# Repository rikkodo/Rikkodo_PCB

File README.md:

# Rikkodo_PCB

PCB関係

## 謝辞

作成には以下の方々のシンボルやフットプリント、知見を利用させていただいています。

Salicylic-acid3 氏のライブラリ[KiCAD_FootPrint](https://github.com/Salicylic-acid3/KiCAD_FootPrint)

koktoh氏のライブラリ [BrownSugar_KBD_KiCad_Library](https://github.com/koktoh/BrownSugar_KBD_KiCad_Library/tree/master)

palette-system氏のライブラリ [az1uball](https://github.com/palette-system/az1uball/tree/main/kicad)

Seeed-Studioのライブラリ [OPL_Kicad_Library](https://github.com/Seeed-Studio/OPL_Kicad_Library?tab=readme-ov-file#jump2)

SparkFunのライブラリ [SparkFun-KiCad-Libraries](https://github.com/sparkfun/SparkFun-KiCad-Libraries.git)

DreaM117er氏のライブラリ [DreaM117er KiCAD Library](https://github.com/DreaM117er/DreaM117er-keebLibrary.git)

Tomotsugu Kaneko氏のライブラリ [BOB-PMW3360-SUMI](https://github.com/snize/BOB-PMW3360-SUMI)

Tomotsugu Kaneko氏のライブラリ [BOB-PMW3360-SEIBOKU](https://github.com/snize/BOB-PMW3610-SEIBOKU)

## ライセンス

### BOB-PMW3360-SUMI、BOB-PMW3360-SEIBOKU

This project is licensed under the CERN OHL-P v2. You may use, distribute, and modify this design under the terms of the CERN OHL-P v2. Original design by snize.

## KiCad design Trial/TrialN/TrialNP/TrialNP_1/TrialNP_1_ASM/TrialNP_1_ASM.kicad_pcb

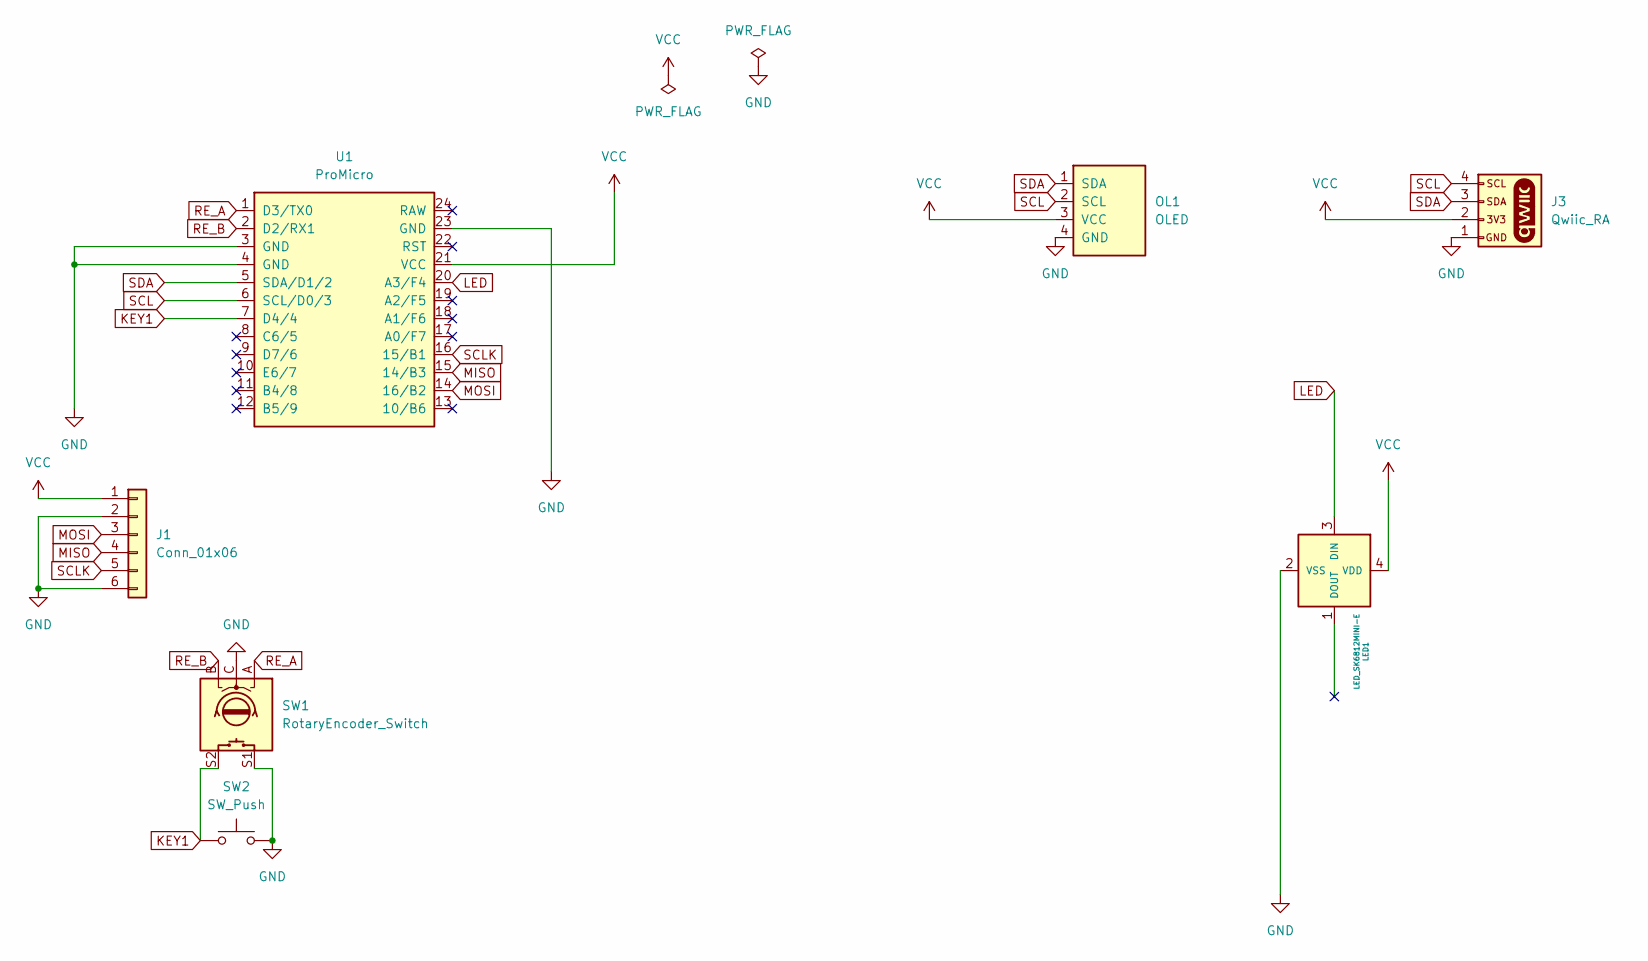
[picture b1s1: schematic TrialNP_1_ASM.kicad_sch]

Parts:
J1: Conn_01x06; PinHeader_1x06_P2.54mm_Vertical
J3: Qwiic_RA; JST_SMD_1.0mm-4_Black
LED1: LED_SK6812MINI-E; LED_SK6812MINI-E_UG
OL1: OLED; OLED_center_display
SW1: RotaryEncoder_Switch; RotaryEncoder_EC11-Switch
SW2: SW_Push; CherryMX_Solder_1u
U1: ProMicro; ProMicro_r

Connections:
GND: J1.2, J1.6, J3.1, LED1.2 (VSS), OL1.4 (GND), SW1.C, SW1.S1, SW2.2, U1.3 (GND), U1.4 (GND), U1.23 (GND)
KEY1: SW1.S2, SW2.1, U1.7 (D4/4)
LED: LED1.3 (DIN), U1.20 (A3/F4)
MISO: J1.4, U1.15 (14/B3)
MOSI: J1.3, U1.14 (16/B2)
RE_A: SW1.A, U1.1 (D3/TX0)
RE_B: SW1.B, U1.2 (D2/RX1)
SCL: J3.4, OL1.2 (SCL), U1.6 (SCL/D0/3)
SCLK: J1.5, U1.16 (15/B1)
SDA: J3.3, OL1.1 (SDA), U1.5 (SDA/D1/2)
VCC: J1.1, J3.2, LED1.4 (VDD), OL1.3 (VCC), U1.21 (VCC)

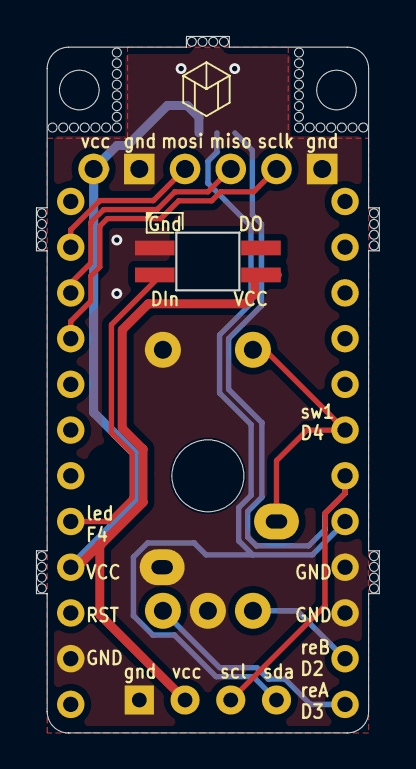
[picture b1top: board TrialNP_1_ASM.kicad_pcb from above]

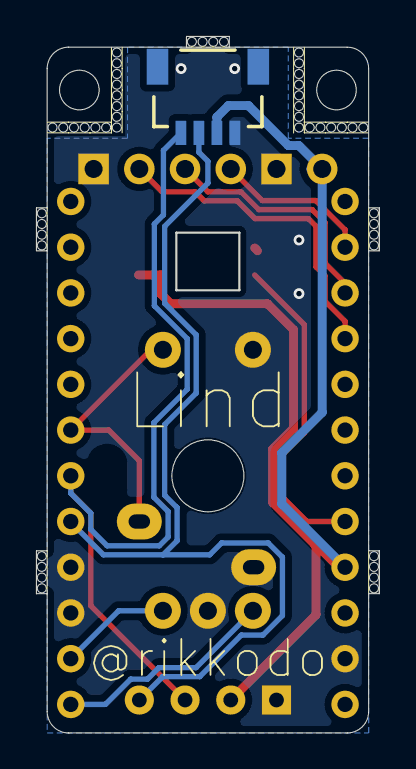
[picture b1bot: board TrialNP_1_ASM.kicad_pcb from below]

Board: 2 copper layers, 19.0 x 38.6 mm, 9 parts (3 on the bottom side), 11 nets.

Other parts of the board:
Ref**: Val**; m2_Screw_Hole
Ref**#2: Val**; m2_Screw_Hole

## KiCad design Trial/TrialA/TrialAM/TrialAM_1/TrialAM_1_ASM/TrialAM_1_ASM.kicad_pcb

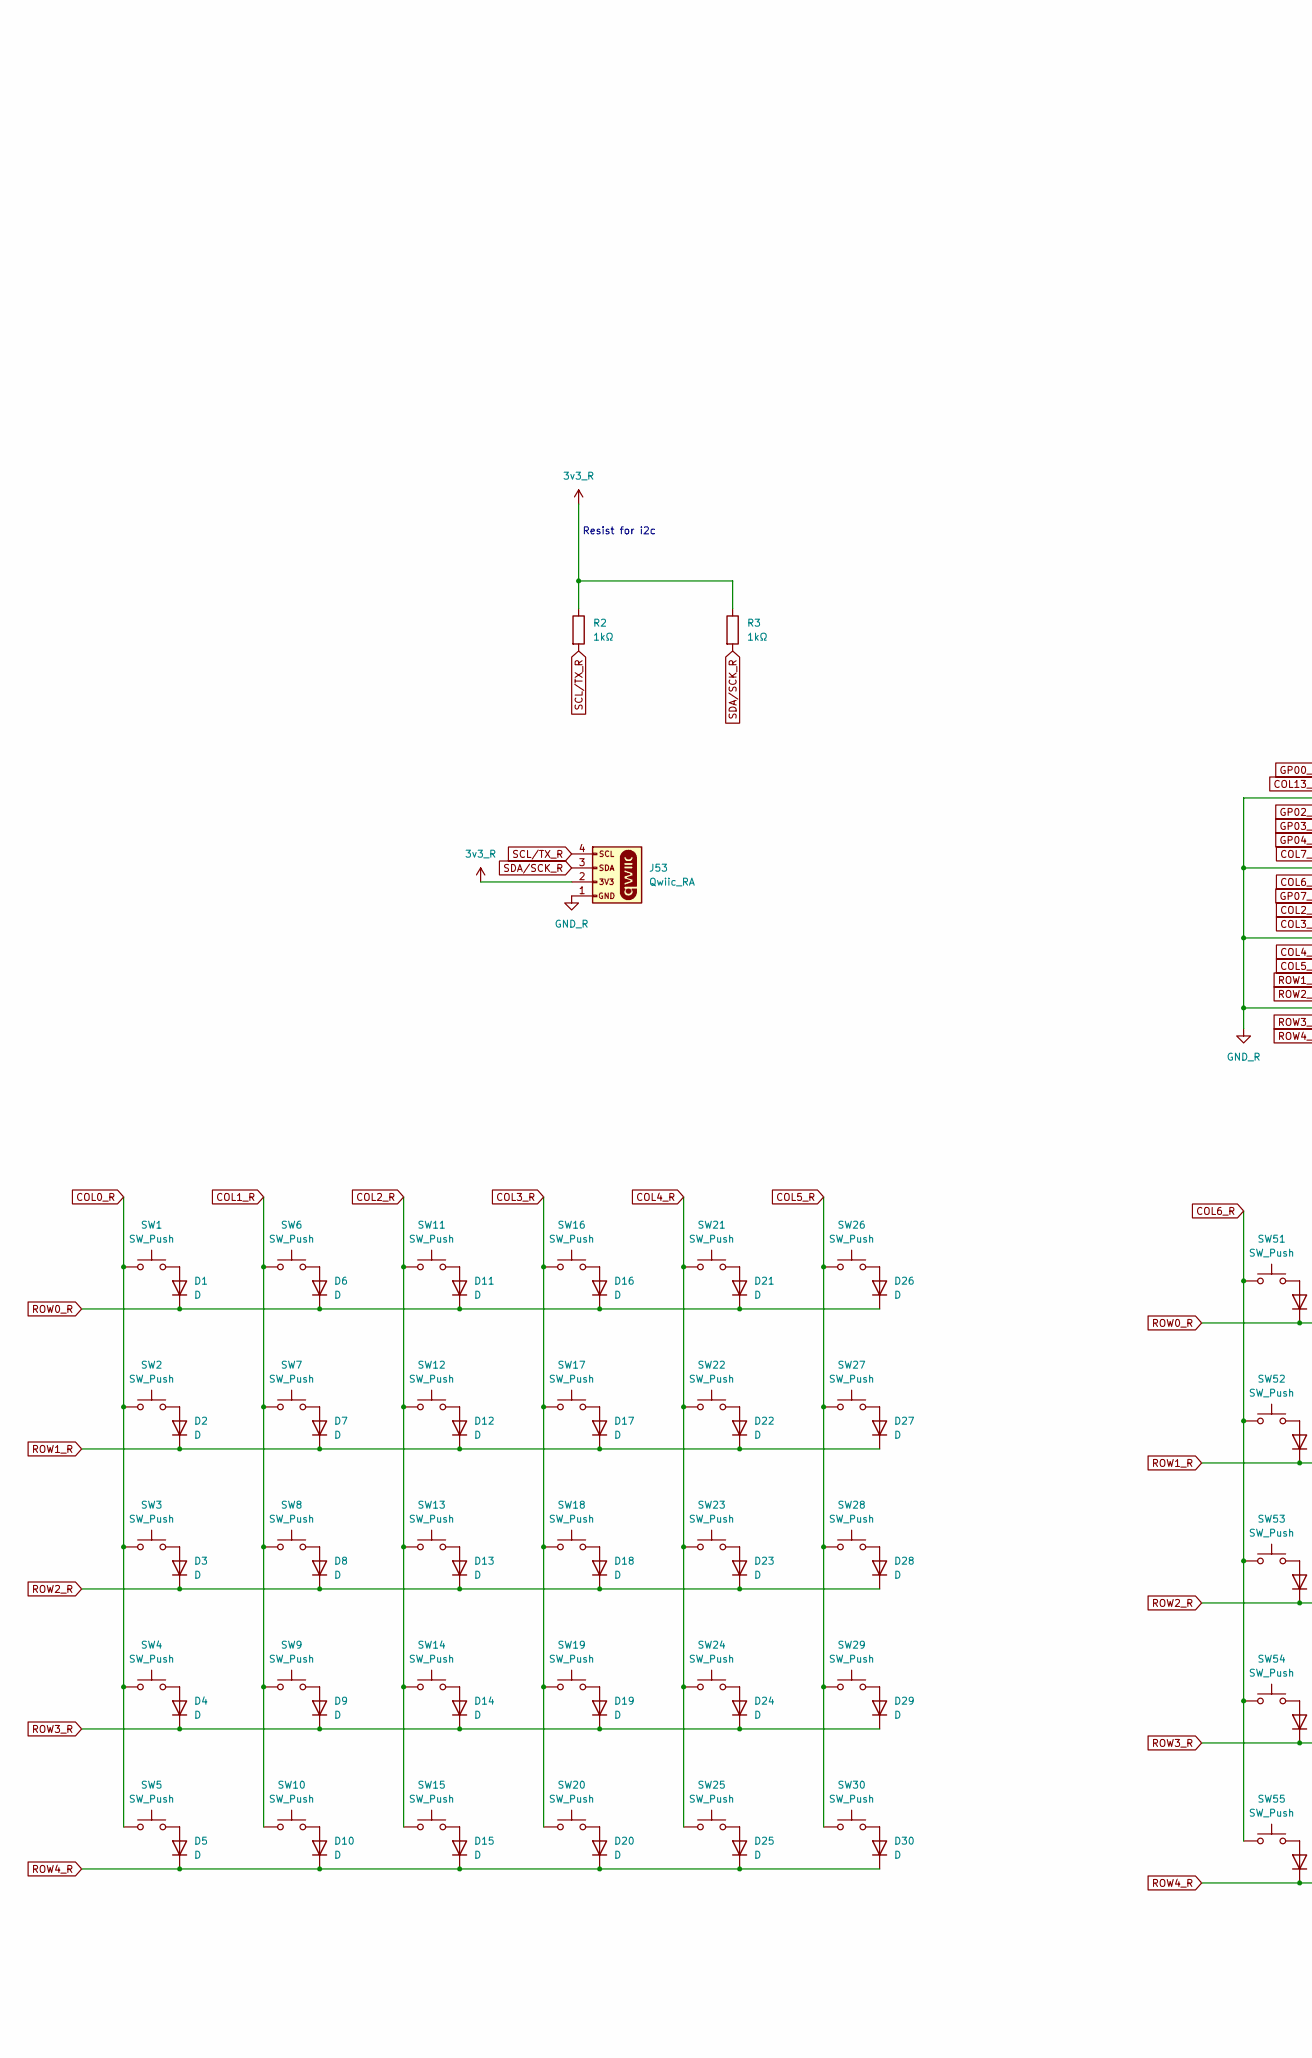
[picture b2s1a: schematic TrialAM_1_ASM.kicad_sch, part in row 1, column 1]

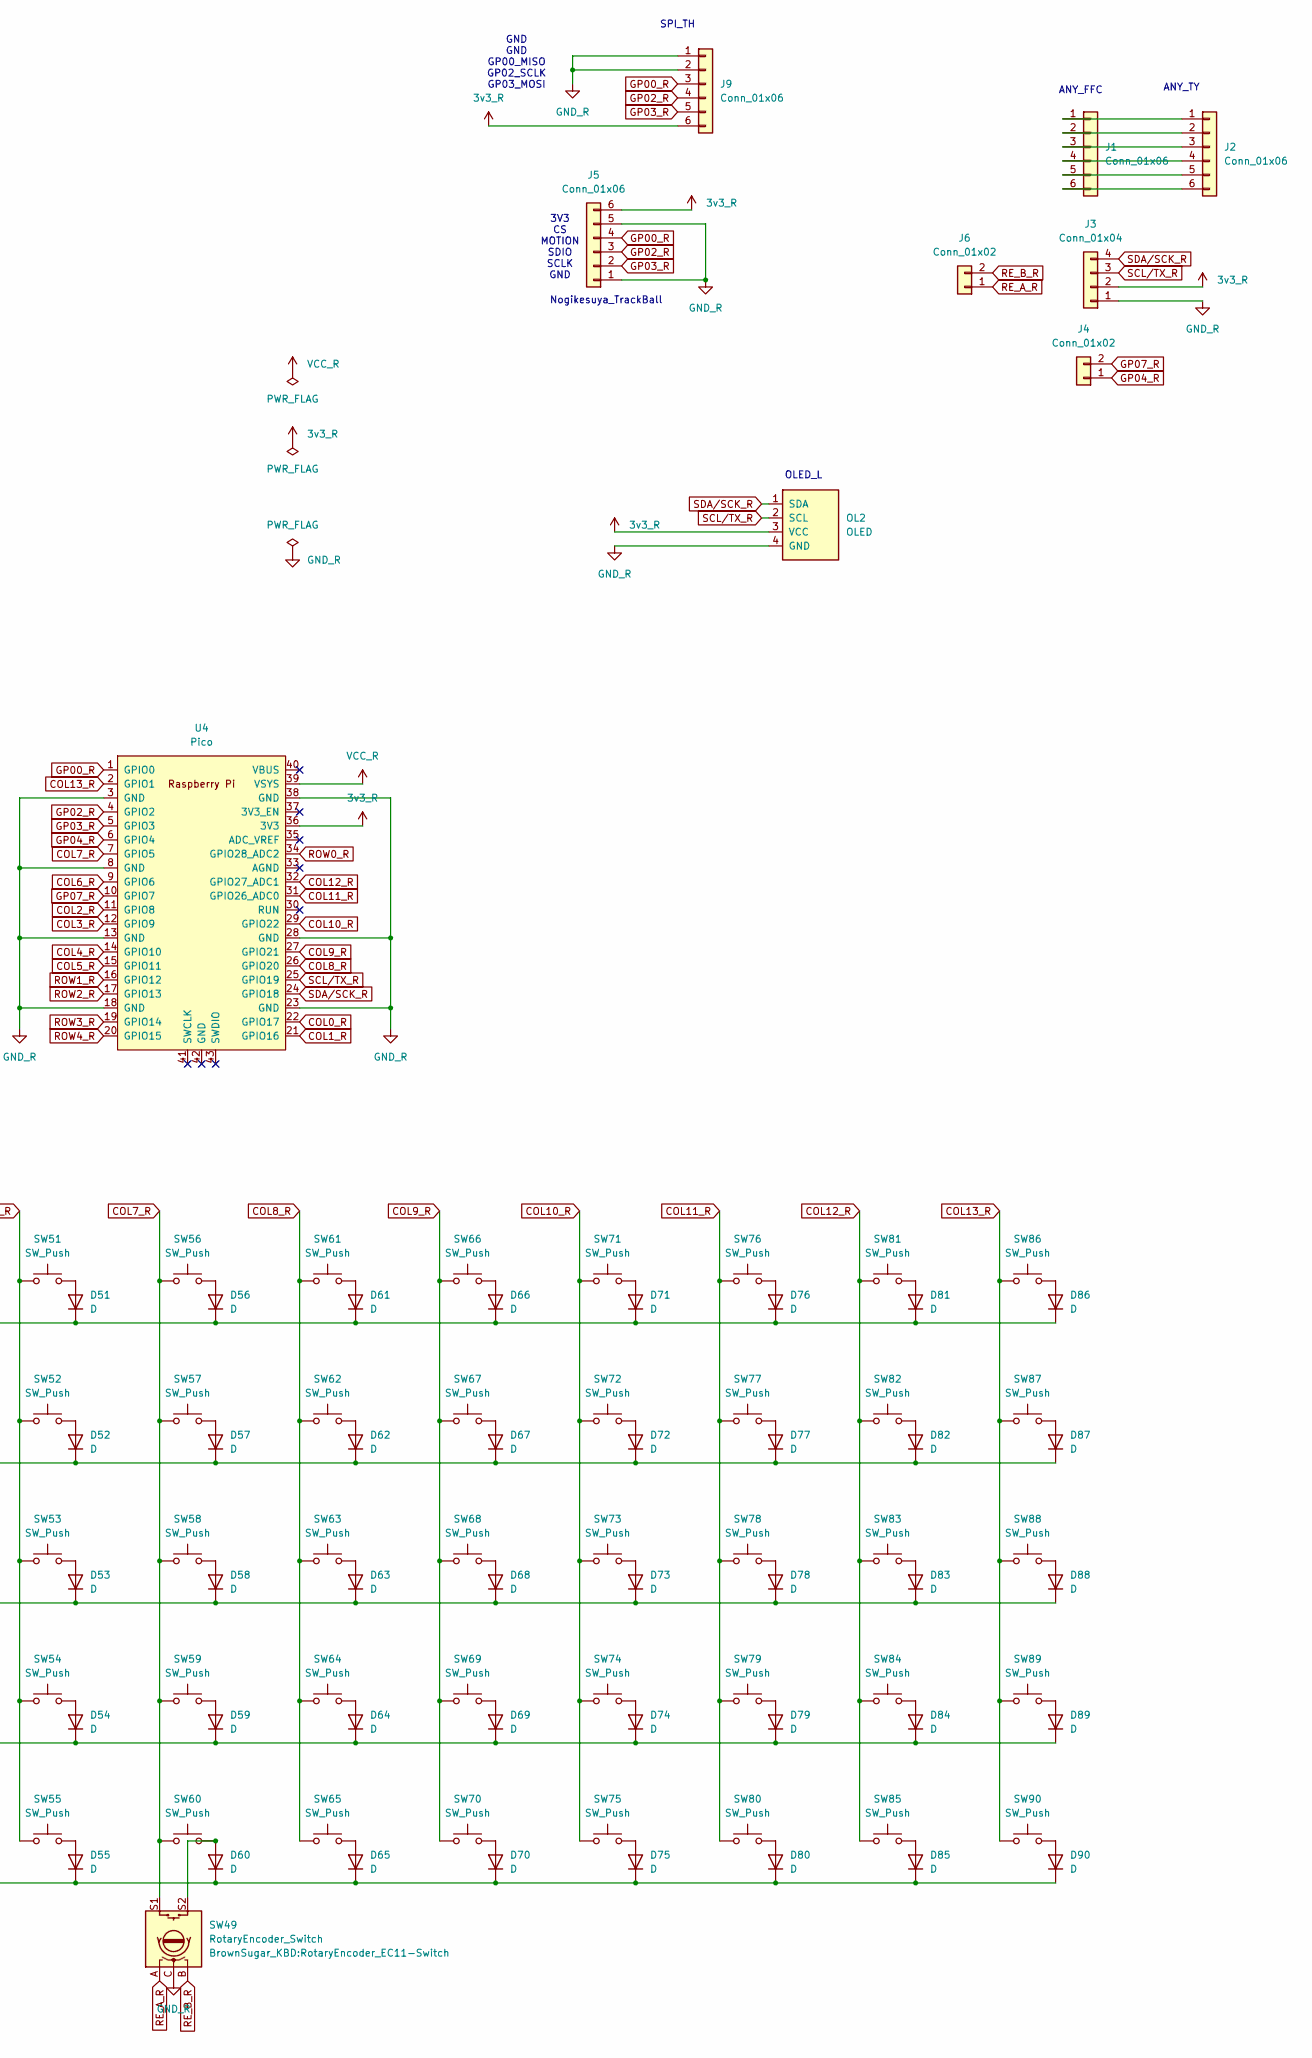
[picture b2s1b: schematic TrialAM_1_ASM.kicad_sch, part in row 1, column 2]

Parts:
D1, D2, D3, D4, D5, D6, D7, D8, D9, D10, D11, D12, D13, D14, D15, D16, D17, D18, D19, D20, D21, D22, D23, D24, D25, D26, D27, D28, D29, D30, D51, D52, D53, D54, D55, D56, D57, D58, D59, D60, D61, D62, D63, D64, D65, D66, D67, D68, D69, D70, D71, D72, D73, D74, D75, D76, D77, D78, D79, D80, D81, D82, D83, D84, D85, D86, D87, D88, D89, D90: D; Diode_SMD
J1, J5: Conn_01x06; Hirose_FH12-6S-0.5SH_1x06-1MP_P0.50mm_Horizontal
J2, J9: Conn_01x06; PinHeader_1x06_P2.54mm_Vertical
J3: Conn_01x04; PinHeader_1x04_P2.54mm_Vertical
J4, J6: Conn_01x02; PinHeader_1x02_P2.54mm_Vertical
J53: Qwiic_RA; JST_SMD_1.0mm-4_Black
OL2: OLED; OLED_center_display
R2, R3: 1kΩ; R_0603_1608Metric
SW1, SW2, SW3, SW4, SW5, SW6, SW7, SW8, SW9, SW10, SW11, SW12, SW13, SW14, SW15, SW16, SW17, SW18, SW19, SW20, SW21, SW22, SW23, SW24, SW26, SW27, SW28, SW29, SW51, SW52, SW54, SW56, SW57, SW58, SW59, SW61, SW62, SW63, SW64, SW65, SW66, SW67, SW68, SW69, SW70, SW71, SW72, SW73, SW74, SW75, SW76, SW77, SW78, SW79, SW80, SW81, SW82, SW83, SW84, SW85, SW86, SW87, SW89, SW90: SW_Push; rkd_pushsw_2_1u
SW25, SW60, SW88: SW_Push; rkd_pushsw_2_2u
SW30, SW53, SW55: SW_Push; rkd_pushsw_2_1.25u
SW49: RotaryEncoder_Switch; RotaryEncoder_EC11-Switch
U4: Pico; rkd_RPi_Pico_TH_NODBG

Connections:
3v3_R: J3.2, J5.6, J9.6, J53.2, OL2.3 (VCC), R2.1, R3.1, U4.36 (3V3)
COL0_R: SW1.2, SW2.2, SW3.2, SW4.2, SW5.2, U4.22 (GPIO17)
COL1_R: SW6.2, SW7.2, SW8.2, SW9.2, SW10.2, U4.21 (GPIO16)
COL2_R: SW11.2, SW12.2, SW13.2, SW14.2, SW15.2, U4.11 (GPIO8)
COL3_R: SW16.2, SW17.2, SW18.2, SW19.2, SW20.2, U4.12 (GPIO9)
COL4_R: SW21.2, SW22.2, SW23.2, SW24.2, SW25.2, U4.14 (GPIO10)
COL5_R: SW26.2, SW27.2, SW28.2, SW29.2, SW30.2, U4.15 (GPIO11)
COL6_R: SW51.2, SW52.2, SW53.2, SW54.2, SW55.2, U4.9 (GPIO6)
COL7_R: SW49.S1, SW56.2, SW57.2, SW58.2, SW59.2, SW60.2, U4.7 (GPIO5)
COL8_R: SW61.2, SW62.2, SW63.2, SW64.2, SW65.2, U4.26 (GPIO20)
COL9_R: SW66.2, SW67.2, SW68.2, SW69.2, SW70.2, U4.27 (GPIO21)
COL10_R: SW71.2, SW72.2, SW73.2, SW74.2, SW75.2, U4.29 (GPIO22)
COL11_R: SW76.2, SW77.2, SW78.2, SW79.2, SW80.2, U4.31 (GPIO26_ADC0)
COL12_R: SW81.2, SW82.2, SW83.2, SW84.2, SW85.2, U4.32 (GPIO27_ADC1)
COL13_R: SW86.2, SW87.2, SW88.2, SW89.2, SW90.2, U4.2 (GPIO1)
GND_R: J3.1, J5.1, J5.5, J9.1, J9.2, J53.1, OL2.4 (GND), SW49.C, U4.3 (GND), U4.8 (GND), U4.13 (GND), U4.18 (GND), U4.23 (GND), U4.28 (GND), U4.38 (GND)
GP00_R: J5.4, J9.3, U4.1 (GPIO0)
GP02_R: J5.3, J9.4, U4.4 (GPIO2)
GP03_R: J5.2, J9.5, U4.5 (GPIO3)
GP04_R: J4.1, U4.6 (GPIO4)
GP07_R: J4.2, U4.10 (GPIO7)
unnamed: D1.2 (A), SW1.1
unnamed: D2.2 (A), SW2.1
unnamed: D3.2 (A), SW3.1
unnamed: D4.2 (A), SW4.1
unnamed: D5.2 (A), SW5.1
unnamed: D6.2 (A), SW6.1
unnamed: D7.2 (A), SW7.1
unnamed: D8.2 (A), SW8.1
unnamed: D9.2 (A), SW9.1
unnamed: D10.2 (A), SW10.1
unnamed: D11.2 (A), SW11.1
unnamed: D12.2 (A), SW12.1
unnamed: D13.2 (A), SW13.1
unnamed: D14.2 (A), SW14.1
unnamed: D15.2 (A), SW15.1
unnamed: D16.2 (A), SW16.1
unnamed: D17.2 (A), SW17.1
unnamed: D18.2 (A), SW18.1
unnamed: D19.2 (A), SW19.1
unnamed: D20.2 (A), SW20.1
unnamed: D21.2 (A), SW21.1
unnamed: D22.2 (A), SW22.1
unnamed: D23.2 (A), SW23.1
unnamed: D24.2 (A), SW24.1
unnamed: D25.2 (A), SW25.1
unnamed: D26.2 (A), SW26.1
unnamed: D27.2 (A), SW27.1
unnamed: D28.2 (A), SW28.1
unnamed: D29.2 (A), SW29.1
unnamed: D30.2 (A), SW30.1
unnamed: D51.2 (A), SW51.1
unnamed: D52.2 (A), SW52.1
unnamed: D53.2 (A), SW53.1
unnamed: D54.2 (A), SW54.1
unnamed: D55.2 (A), SW55.1
unnamed: D56.2 (A), SW56.1
unnamed: D57.2 (A), SW57.1
unnamed: D58.2 (A), SW58.1
unnamed: D59.2 (A), SW59.1
unnamed: D60.2 (A), SW49.S2, SW60.1
unnamed: D61.2 (A), SW61.1
unnamed: D62.2 (A), SW62.1
unnamed: D63.2 (A), SW63.1
unnamed: D64.2 (A), SW64.1
unnamed: D65.2 (A), SW65.1
unnamed: D66.2 (A), SW66.1
unnamed: D67.2 (A), SW67.1
unnamed: D68.2 (A), SW68.1
unnamed: D69.2 (A), SW69.1
unnamed: D70.2 (A), SW70.1
unnamed: D71.2 (A), SW71.1
unnamed: D72.2 (A), SW72.1
unnamed: D73.2 (A), SW73.1
unnamed: D74.2 (A), SW74.1
unnamed: D75.2 (A), SW75.1
unnamed: D76.2 (A), SW76.1
unnamed: D77.2 (A), SW77.1
unnamed: D78.2 (A), SW78.1
unnamed: D79.2 (A), SW79.1
unnamed: D80.2 (A), SW80.1
unnamed: D81.2 (A), SW81.1
unnamed: D82.2 (A), SW82.1
unnamed: D83.2 (A), SW83.1
unnamed: D84.2 (A), SW84.1
unnamed: D85.2 (A), SW85.1
unnamed: D86.2 (A), SW86.1
unnamed: D87.2 (A), SW87.1
unnamed: D88.2 (A), SW88.1
unnamed: D89.2 (A), SW89.1
unnamed: D90.2 (A), SW90.1
unnamed: J1.1, J2.1
unnamed: J1.2, J2.2
unnamed: J1.3, J2.3
unnamed: J1.4, J2.4
unnamed: J1.5, J2.5
unnamed: J1.6, J2.6
RE_A_R: J6.1, SW49.A
RE_B_R: J6.2, SW49.B
ROW0_R: D1.1 (K), D6.1 (K), D11.1 (K), D16.1 (K), D21.1 (K), D26.1 (K), D51.1 (K), D56.1 (K), D61.1 (K), D66.1 (K), D71.1 (K), D76.1 (K), D81.1 (K), D86.1 (K), U4.34 (GPIO28_ADC2)
ROW1_R: D2.1 (K), D7.1 (K), D12.1 (K), D17.1 (K), D22.1 (K), D27.1 (K), D52.1 (K), D57.1 (K), D62.1 (K), D67.1 (K), D72.1 (K), D77.1 (K), D82.1 (K), D87.1 (K), U4.16 (GPIO12)
ROW2_R: D3.1 (K), D8.1 (K), D13.1 (K), D18.1 (K), D23.1 (K), D28.1 (K), D53.1 (K), D58.1 (K), D63.1 (K), D68.1 (K), D73.1 (K), D78.1 (K), D83.1 (K), D88.1 (K), U4.17 (GPIO13)
ROW3_R: D4.1 (K), D9.1 (K), D14.1 (K), D19.1 (K), D24.1 (K), D29.1 (K), D54.1 (K), D59.1 (K), D64.1 (K), D69.1 (K), D74.1 (K), D79.1 (K), D84.1 (K), D89.1 (K), U4.19 (GPIO14)
ROW4_R: D5.1 (K), D10.1 (K), D15.1 (K), D20.1 (K), D25.1 (K), D30.1 (K), D55.1 (K), D60.1 (K), D65.1 (K), D70.1 (K), D75.1 (K), D80.1 (K), D85.1 (K), D90.1 (K), U4.20 (GPIO15)
SCL/TX_R: J3.3, J53.4, OL2.2 (SCL), R2.2, U4.25 (GPIO19)
SDA/SCK_R: J3.4, J53.3, OL2.1 (SDA), R3.2, U4.24 (GPIO18)
VCC_R: U4.39 (VSYS)

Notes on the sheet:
GND GND GP00_MISO GP02_SCLK GP03_MOSI
Resist for i2c
ANY_TY
3V3 CS MOTION SDIO SCLK GND
ANY_FFC
Nogikesuya_TrackBall
SPI_TH
OLED_L

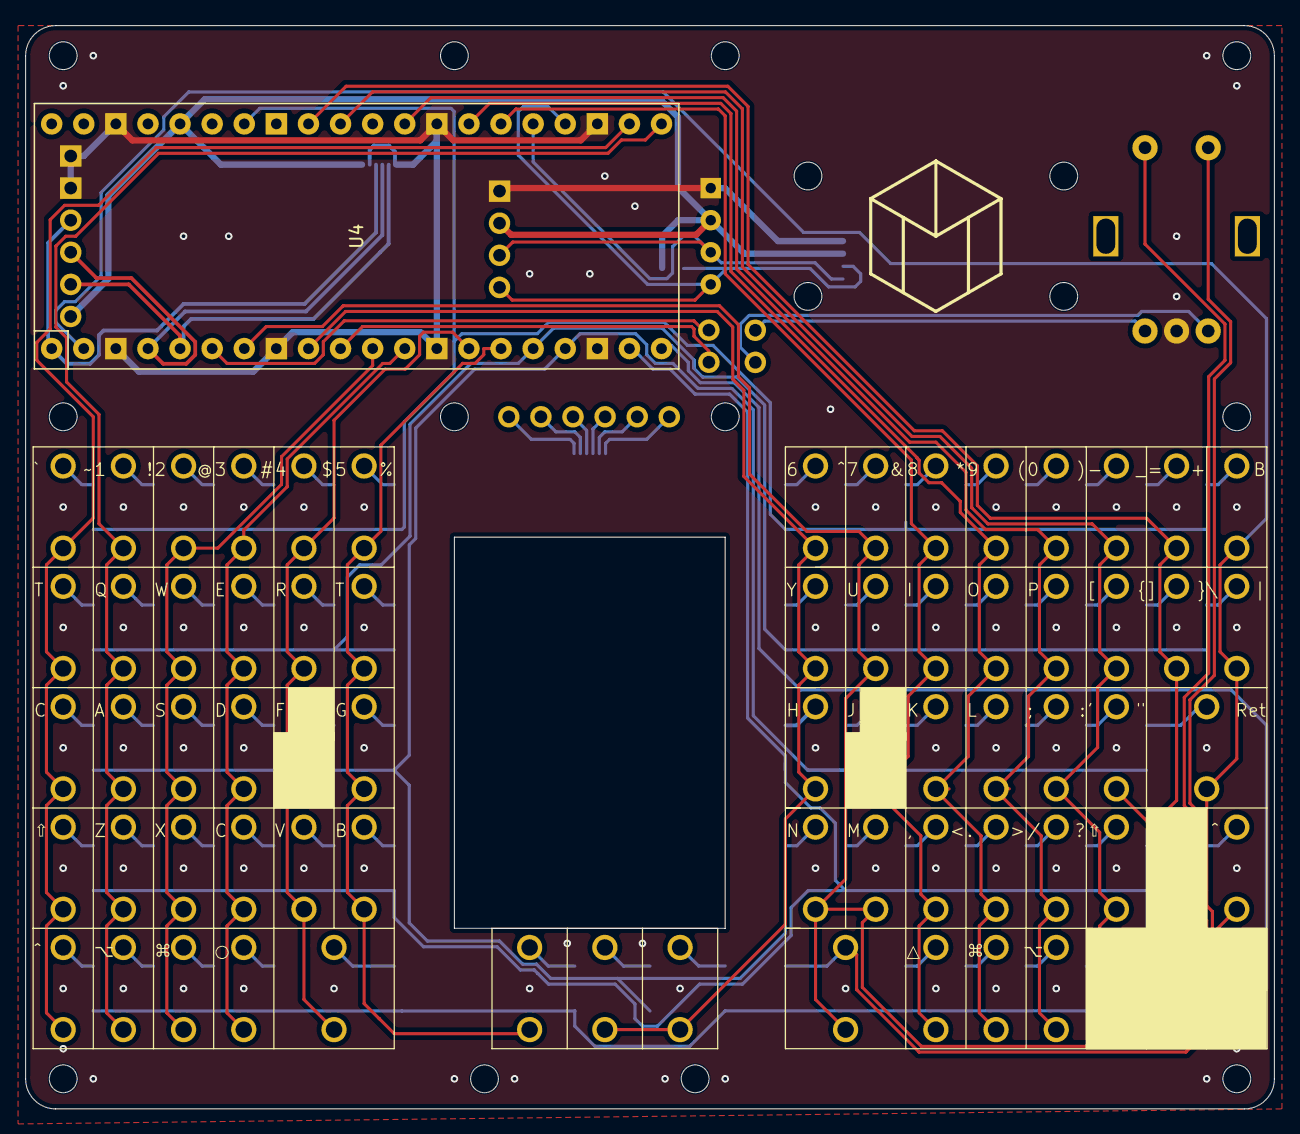
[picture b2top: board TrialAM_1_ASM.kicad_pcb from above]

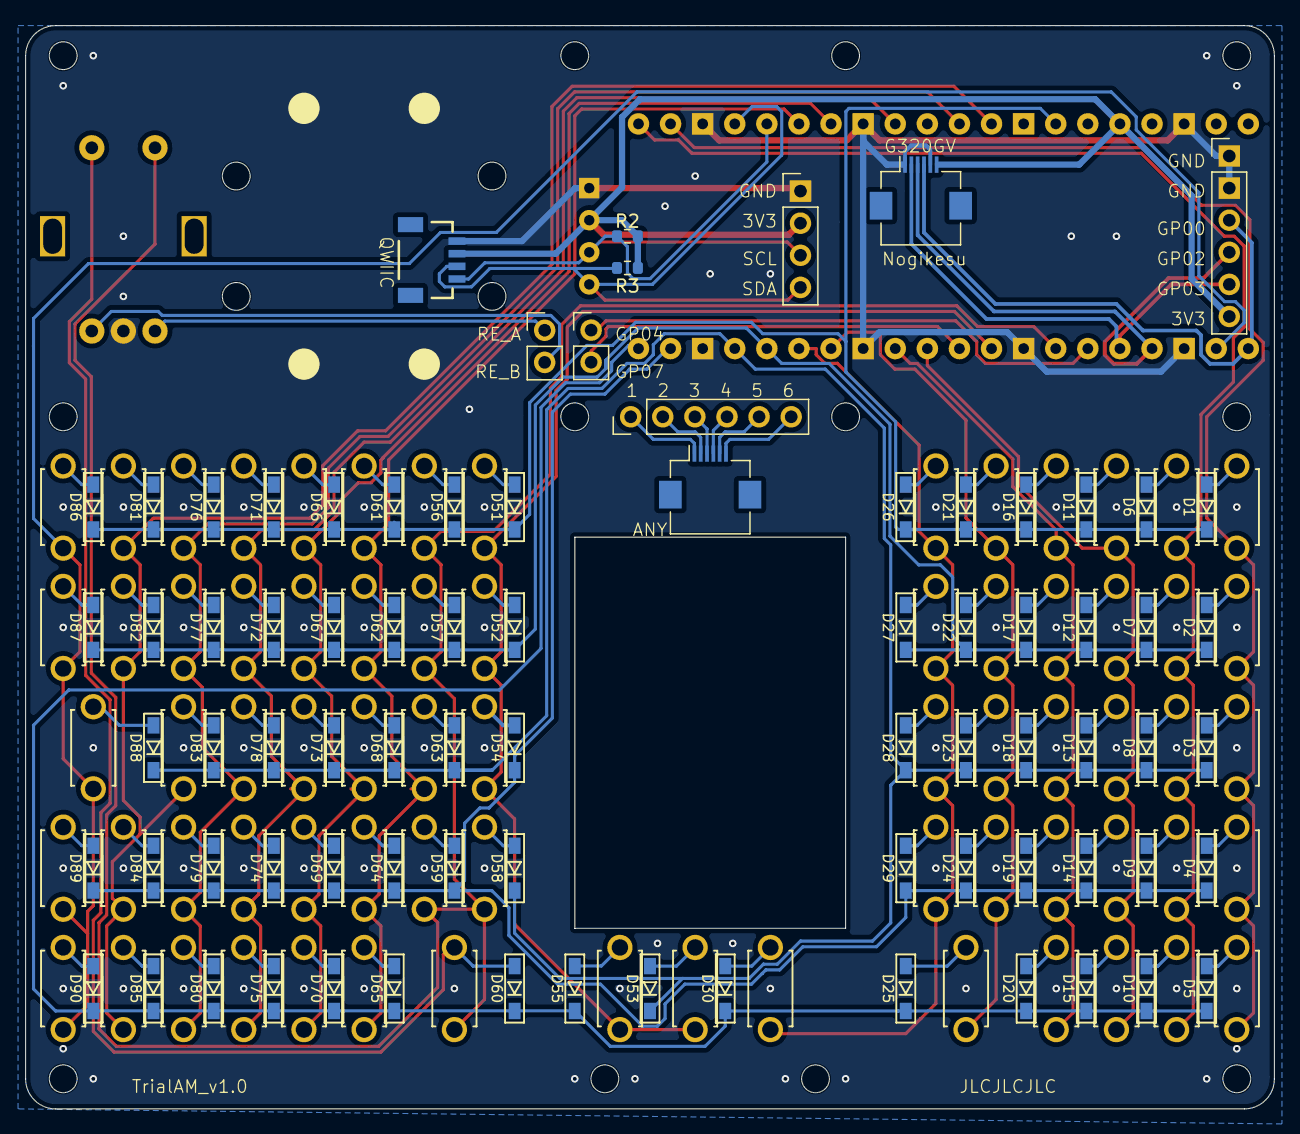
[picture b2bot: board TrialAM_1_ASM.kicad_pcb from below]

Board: 2 copper layers, 98.8 x 85.7 mm, 168 parts (10 on the bottom side), 106 nets.

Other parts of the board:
Point1: Guard_Screw_Hall; rkd_Guard_Screw_Hall
Ref**: Val**; m2_Screw_Hole
Ref**#2, Ref**#3, Ref**#4, Ref**#5, Ref**#6, Ref**#7, Ref**#8, Ref**#9, Ref**#10, Ref**#11, Ref**#12, Ref**#13, Ref**#14: Val**; m2_Screw_Hole

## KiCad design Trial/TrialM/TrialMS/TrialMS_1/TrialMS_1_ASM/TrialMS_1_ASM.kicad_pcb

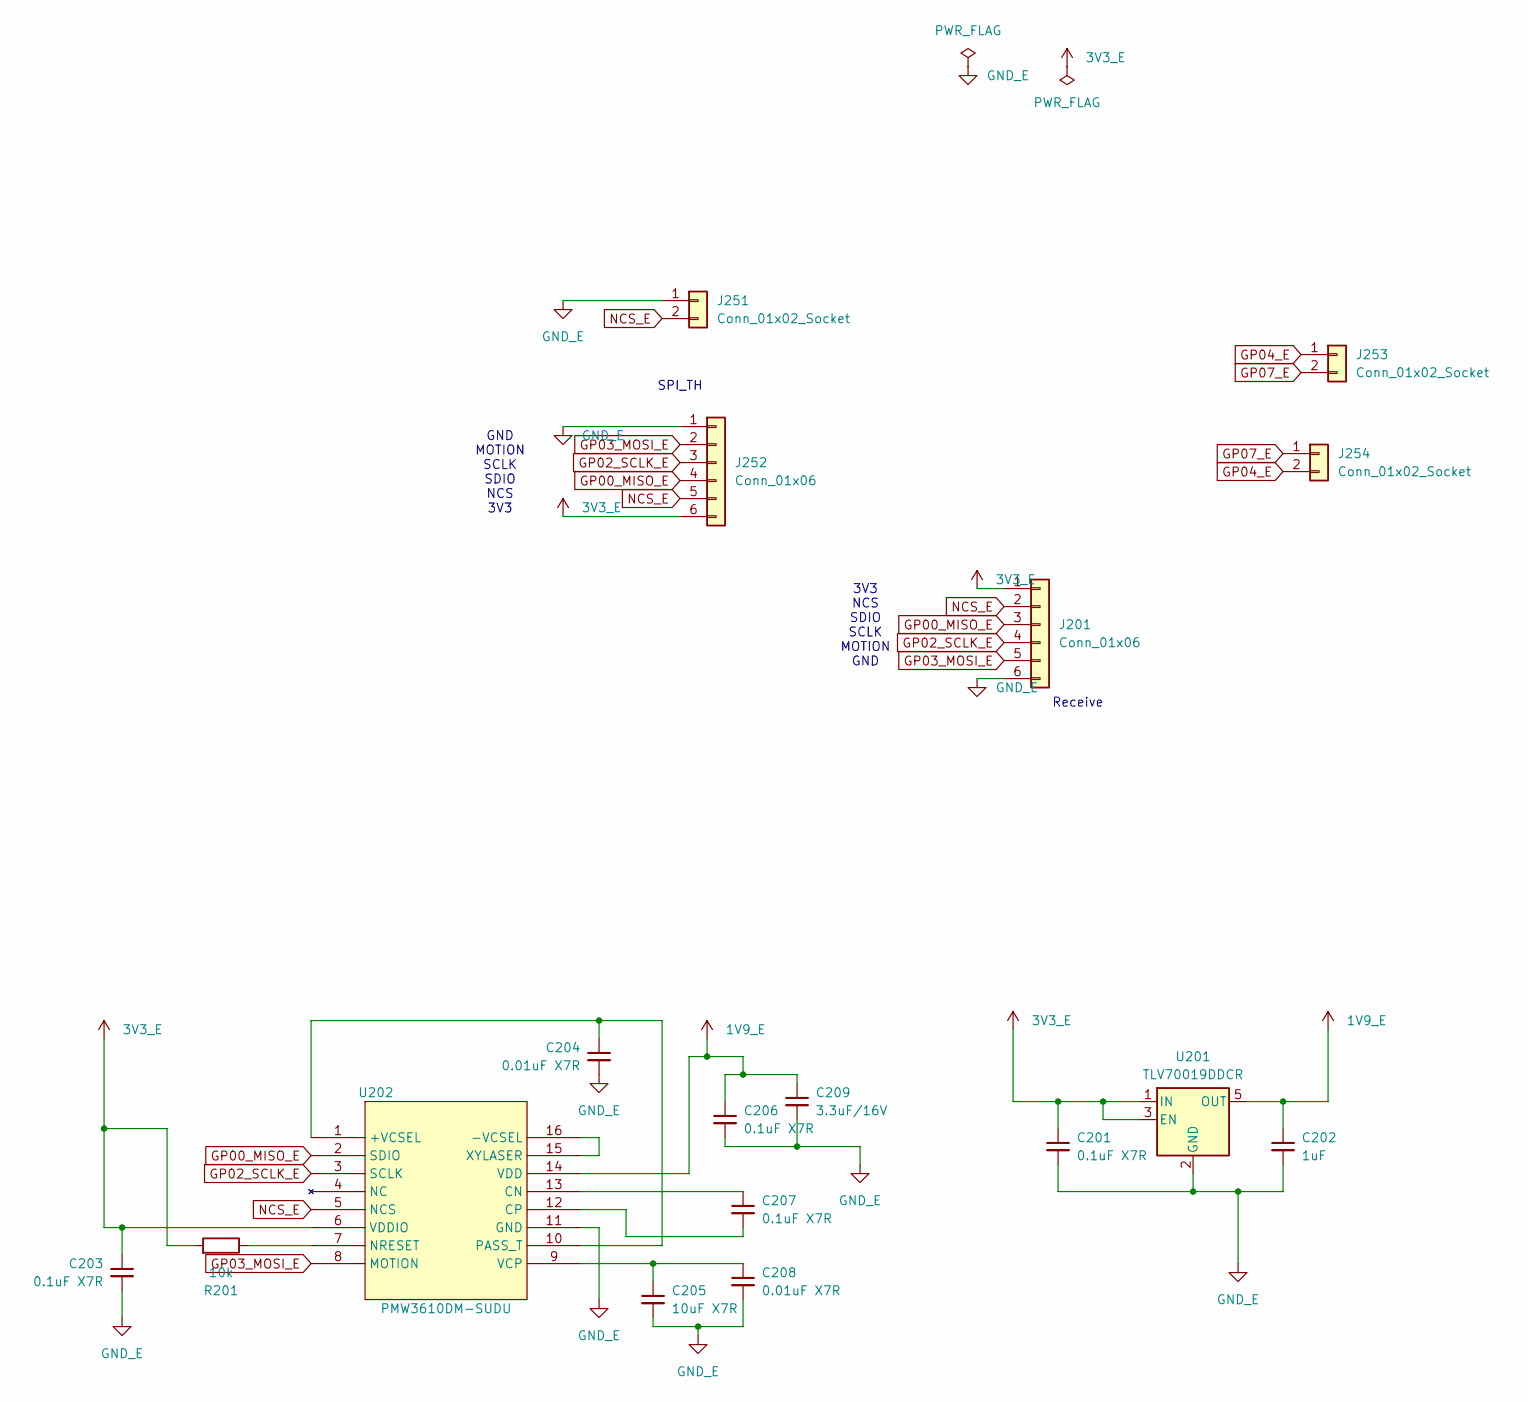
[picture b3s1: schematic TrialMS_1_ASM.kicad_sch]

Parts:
C201, C203, C206, C207: 0.1uF X7R; C_0805_2012Metric_Pad1.18x1.45mm_HandSolder
C202: 1uF; C_0805_2012Metric_Pad1.18x1.45mm_HandSolder
C204, C208: 0.01uF X7R; C_0805_2012Metric_Pad1.18x1.45mm_HandSolder
C205: 10uF X7R; C_0805_2012Metric_Pad1.18x1.45mm_HandSolder
C209: 3.3uF/16V; C_0805_2012Metric_Pad1.18x1.45mm_HandSolder
J201: Conn_01x06; Hirose_FH12-6S-0.5SH_1x06-1MP_P0.50mm_Horizontal
J251, J253, J254: Conn_01x02_Socket; PinHeader_1x02_P2.54mm_Vertical
J252: Conn_01x06; PinHeader_1x06_P2.54mm_Vertical
R201: 10k; R_0805_2012Metric_Pad1.20x1.40mm_HandSolder
U201: TLV70019DDCR; SOT-23-5_HandSoldering
U202: PMW3610DM-SUDU

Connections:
1V9_E: C202.1, C206.1, C209.1, U201.5 (OUT), U202.14 (VDD)
3V3_E: C201.1, C203.1, J201.1, J252.6, R201.2, U201.1 (IN), U201.3 (EN), U202.6 (VDDIO)
GND_E: C201.2, C202.2, C203.2, C204.2, C205.2, C206.2, C208.2, C209.2, J201.6, J251.1, J252.1, U201.2 (GND), U202.11 (GND)
GP00_MISO_E: J201.3, J252.4, U202.2 (SDIO)
GP02_SCLK_E: J201.4, J252.3, U202.3 (SCLK)
GP03_MOSI_E: J201.5, J252.2, U202.8 (MOTION)
GP04_E: J253.1, J254.2
GP07_E: J253.2, J254.1
NCS_E: J201.2, J251.2, J252.5, U202.5 (NCS)
unnamed: C204.1, U202.1 (+VCSEL), U202.10 (PASS_T)
unnamed: U202.15 (XYLASER), U202.16 (-VCSEL)
unnamed: C207.1, U202.13 (CN)
unnamed: C207.2, U202.12 (CP)
unnamed: R201.1, U202.7 (NRESET)
unnamed: C205.1, C208.1, U202.9 (VCP)

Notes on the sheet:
SPI_TH
GND MOTION SCLK SDIO NCS 3V3
Receive
3V3 NCS SDIO SCLK MOTION GND

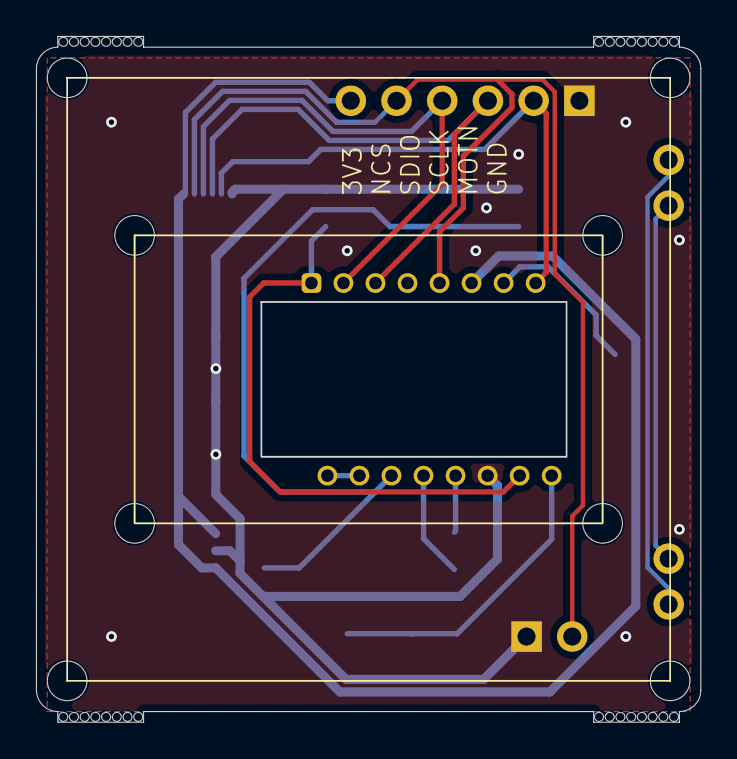
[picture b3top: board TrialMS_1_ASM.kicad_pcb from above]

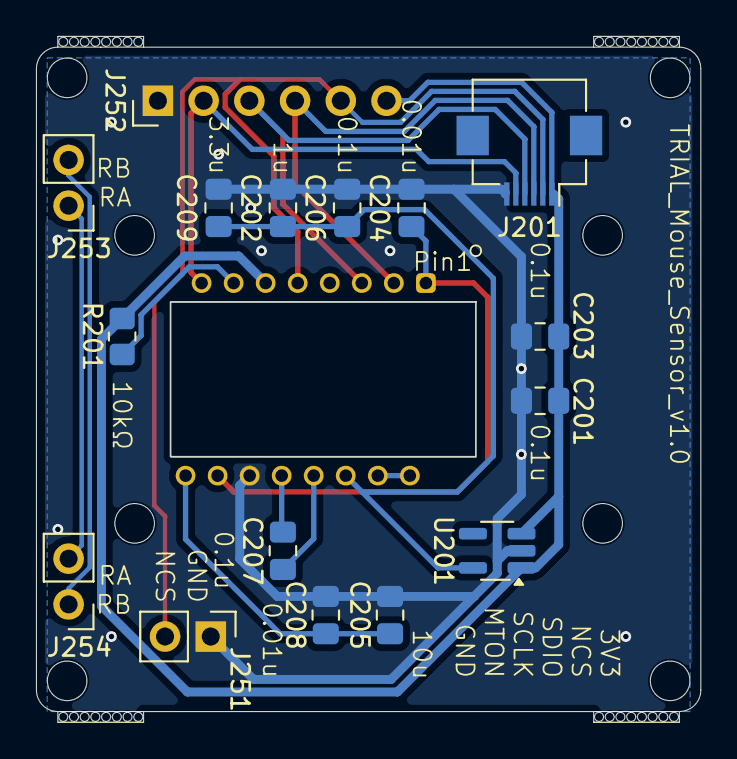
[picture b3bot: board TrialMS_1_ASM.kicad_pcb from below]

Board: 2 copper layers, 36.9 x 38.0 mm, 18 parts (16 on the bottom side), 15 nets.

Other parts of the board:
Picot**: rkd_picot5400_BTM
